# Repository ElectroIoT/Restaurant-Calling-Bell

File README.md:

# Restaurant Calling Bell (SI24R1)

Open-source wireless table-calling system: **10 table remotes** (ATmega328P + SI24R1, coin cell or 2xAAA) and **one counter receiver**
(ATmega328P + SI24R1 + SSD1306 OLED + DFPlayer Mini voice). Application-level acknowledgement, bounded retries, duplicate suppression,
pending calls that survive a power cut.

**Status (2026-10-29): firmware compiles, protocol logic tested in software, no hardware tested yet.** See
[docs/hardware-verification.md](docs/hardware-verification.md) for exactly what is verified. Full plan with advice: open
[docs/plan.html](docs/plan.html) in a browser.

The earlier ATtiny85/STM32 concept is kept in `docs/archive-v0-attiny-stm32/`. Vendor datasheets: `docs/datasheets/`.

## Layout

```
docs/        plan.html, architecture, protocol, radio driver choice, audio, power/safety, battery, assembly, flashing,
             troubleshooting, test plan, EasyEDA guide, hardware verification, datasheets
firmware/    common/ (library: protocol, call table, retry FSM, EEPROM log, radio driver), remote/, receiver/
hardware/    remote/ receiver/ (BOM CSVs, EasyEDA data pack, KiCad REFERENCE boards), diagrams/ (Mermaid + wiring), bom/, tools/
tests/       protocol-tests/ (host C tests + 10-remote simulation), test-results-template.csv
tools/       build_firmware.py, battery_calc.py, make_audio_windows.ps1
```

## Quick start

```bash
python tools/build_firmware.py --quick        # compile one remote + receiver for Uno and PCB targets
python tools/build_firmware.py                # all 22 builds, hex files in build/hex/
python tests/protocol-tests/run_tests.py      # host tests (gcc/clang, or: pip install --target tools/.zig ziglang)
python tools/battery_calc.py                  # battery estimate (assumptions, not measurements)
python hardware/tools/gen_bom.py              # regenerate BOM CSVs from hardware/tools/*_design.py
```

Toolchain used: arduino-cli 1.5.1 (inside Arduino IDE 2), `arduino:avr` 1.8.8 (avr-gcc 7.3). Per-board build properties are in
[docs/flashing-guide.md](docs/flashing-guide.md). Table id: `-DTABLE_ID=n` (1..10, checked at compile time).

## Where to start

1. Read [docs/plan.html](docs/plan.html), then [docs/test-plan.md](docs/test-plan.md).
2. Build the two-Uno prototype ([wiring](hardware/diagrams/wiring.md)) and pass tests 2-9.
3. Lay out the PCBs in EasyEDA Pro from [hardware/*/easyeda](hardware) and [docs/easyeda-guide.md](docs/easyeda-guide.md).
4. Order parts from [hardware/bom/BOM-SUMMARY.md](hardware/bom/BOM-SUMMARY.md) (check the "needs checking" list first).

## Known limits

No range, battery-life or reliability number here is measured. The coin-cell option depends on a sag test you still have to run. DFPlayer pin
order/spacing and the coin-holder polarity are assumptions. No audio files are included. KiCad boards in `hardware/*/kicad` are an
unreviewed auto-routed reference, not a release.

## Licence

MIT, see [LICENSE](LICENSE) (firmware, tools, docs and design data).

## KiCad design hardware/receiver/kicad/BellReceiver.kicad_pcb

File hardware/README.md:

# Hardware

You lay the boards out yourself in **EasyEDA Pro**. Start with [`../docs/easyeda-guide.md`](../docs/easyeda-guide.md).

| Folder | Content |
|---|---|
| `remote/easyeda`, `receiver/easyeda` | netlist, per-pin nets, BOM with LCSC numbers, placement hints (generated from `tools/*_design.py`) |
| `remote/bom`, `receiver/bom`, `bom/` | BOM CSVs (1x, 10x, system) and `BOM-SUMMARY.md` |
| `remote/kicad`, `receiver/kicad` | **reference only**: KiCad 10 schematic and an auto-routed PCB. ERC and DRC were run (0 errors on the last runs, silkscreen warnings only). Not reviewed by a person, not fabricated. |
| `lib/BellParts.pretty` | KiCad footprints for the SI24R1 module, CR2450 holder and tact switch, from vendor drawings (polarity of the holder unknown) |
| `diagrams/` | Mermaid block, sequence and state diagrams, `wiring.md` pin maps |
| `tools/` | generators: schematic/PCB for KiCad (adapted from the NewYearPixelFireworks scripts), `gen_bom.py`, `gen_easyeda_pack.py`; Freerouting jar is not committed |

Single source of truth: `tools/remote_design.py` and `tools/receiver_design.py`.

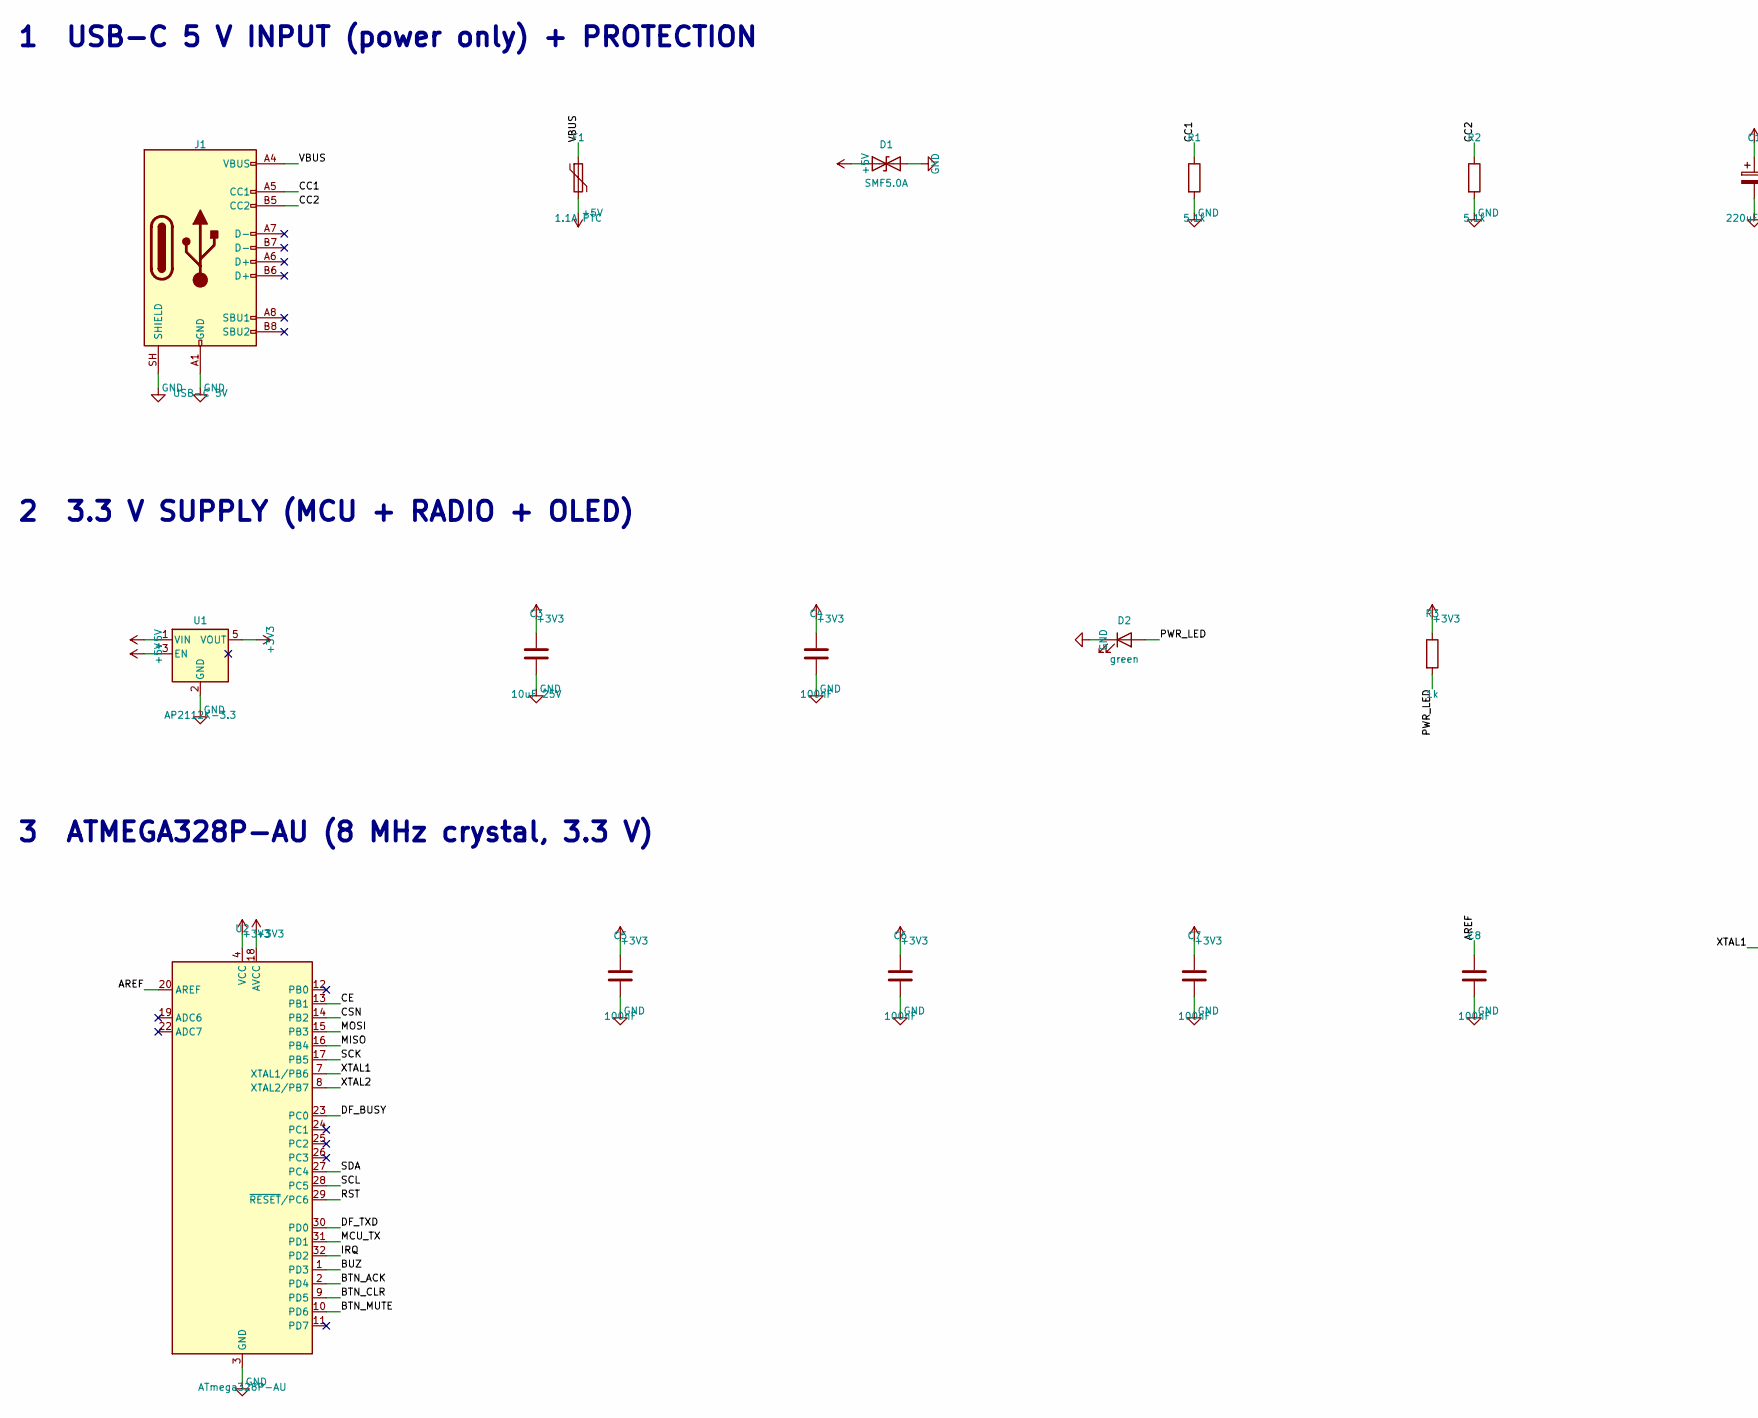
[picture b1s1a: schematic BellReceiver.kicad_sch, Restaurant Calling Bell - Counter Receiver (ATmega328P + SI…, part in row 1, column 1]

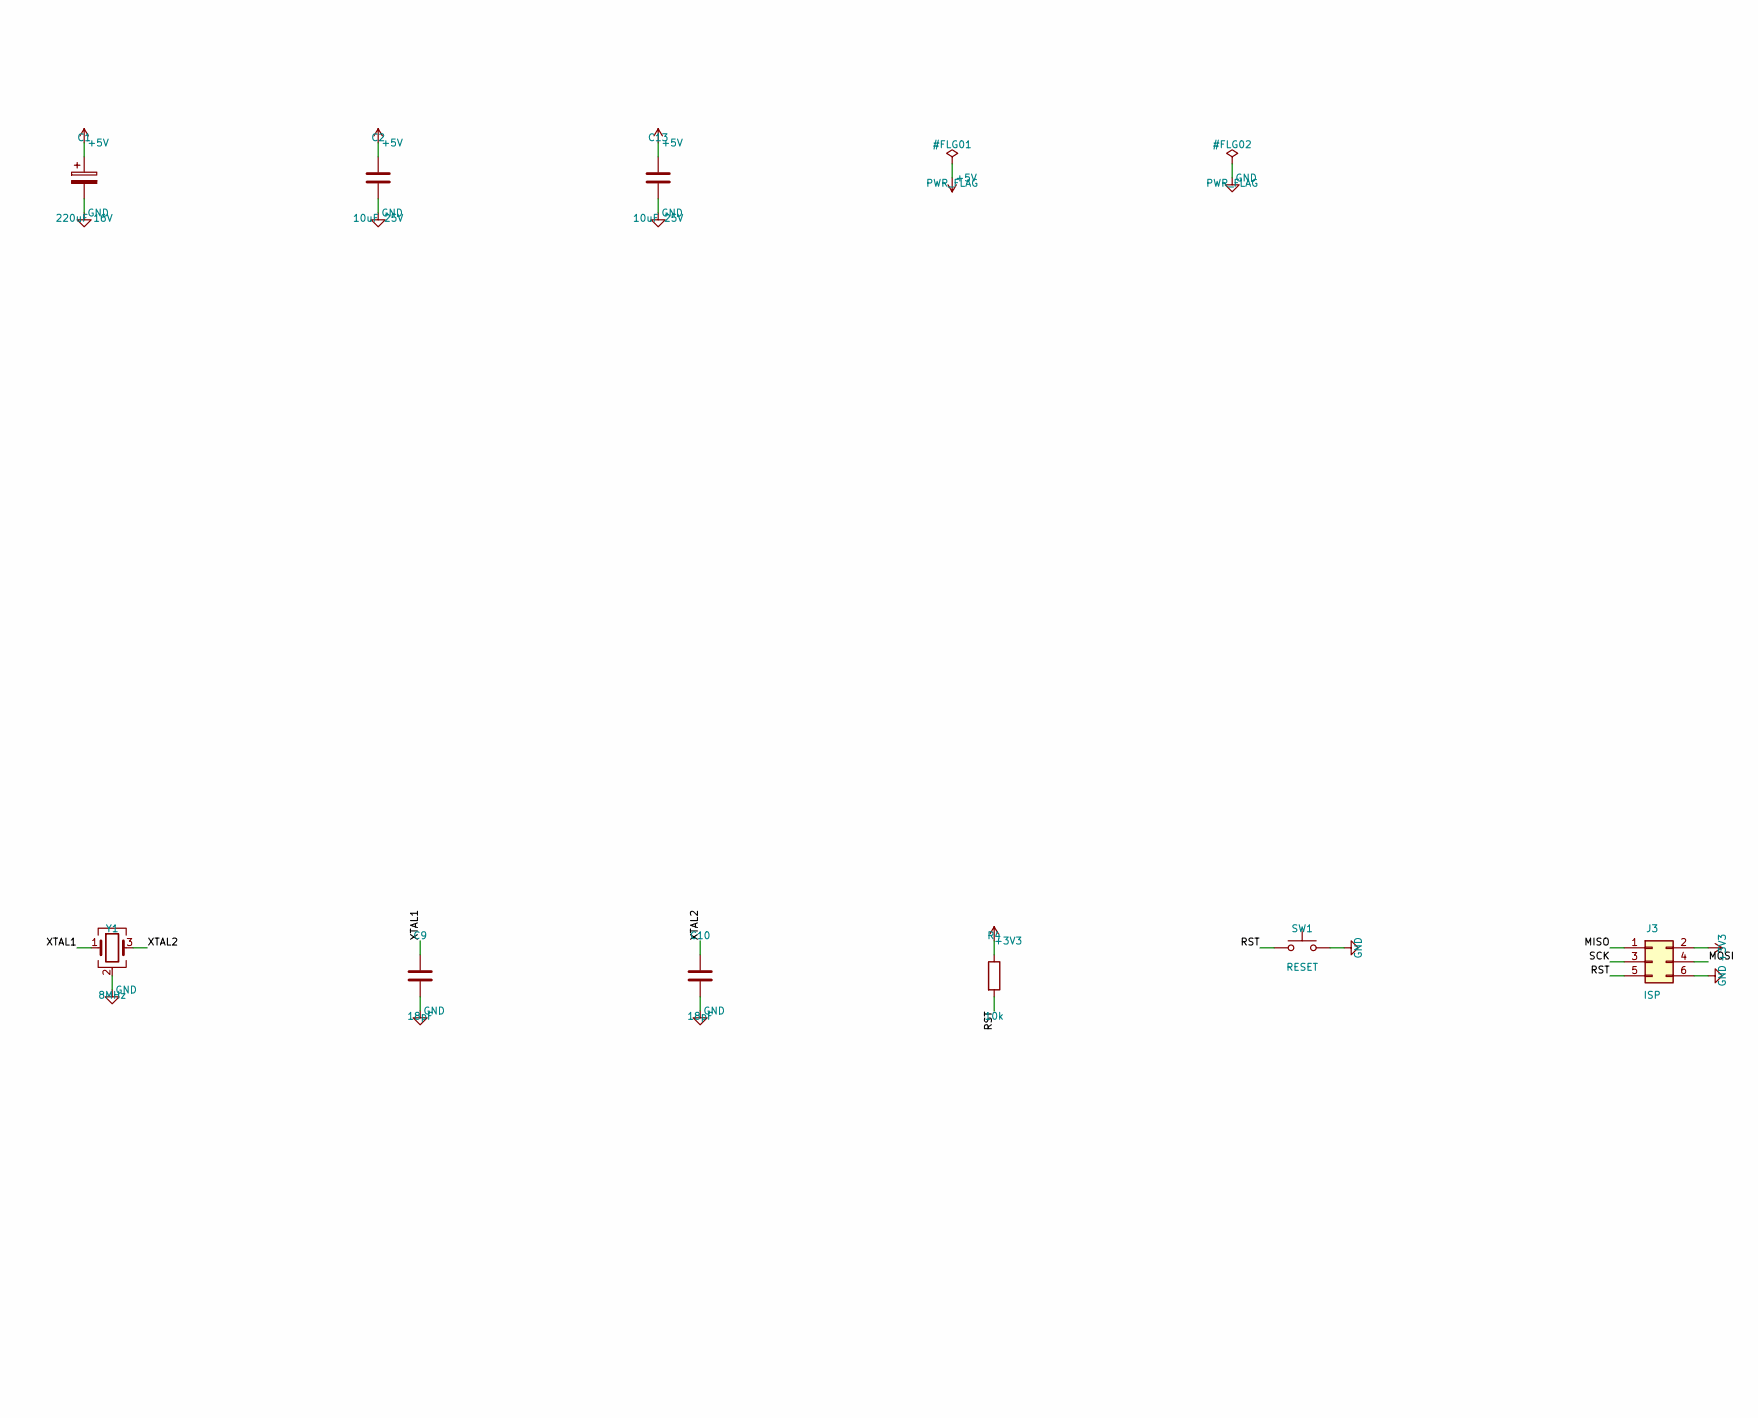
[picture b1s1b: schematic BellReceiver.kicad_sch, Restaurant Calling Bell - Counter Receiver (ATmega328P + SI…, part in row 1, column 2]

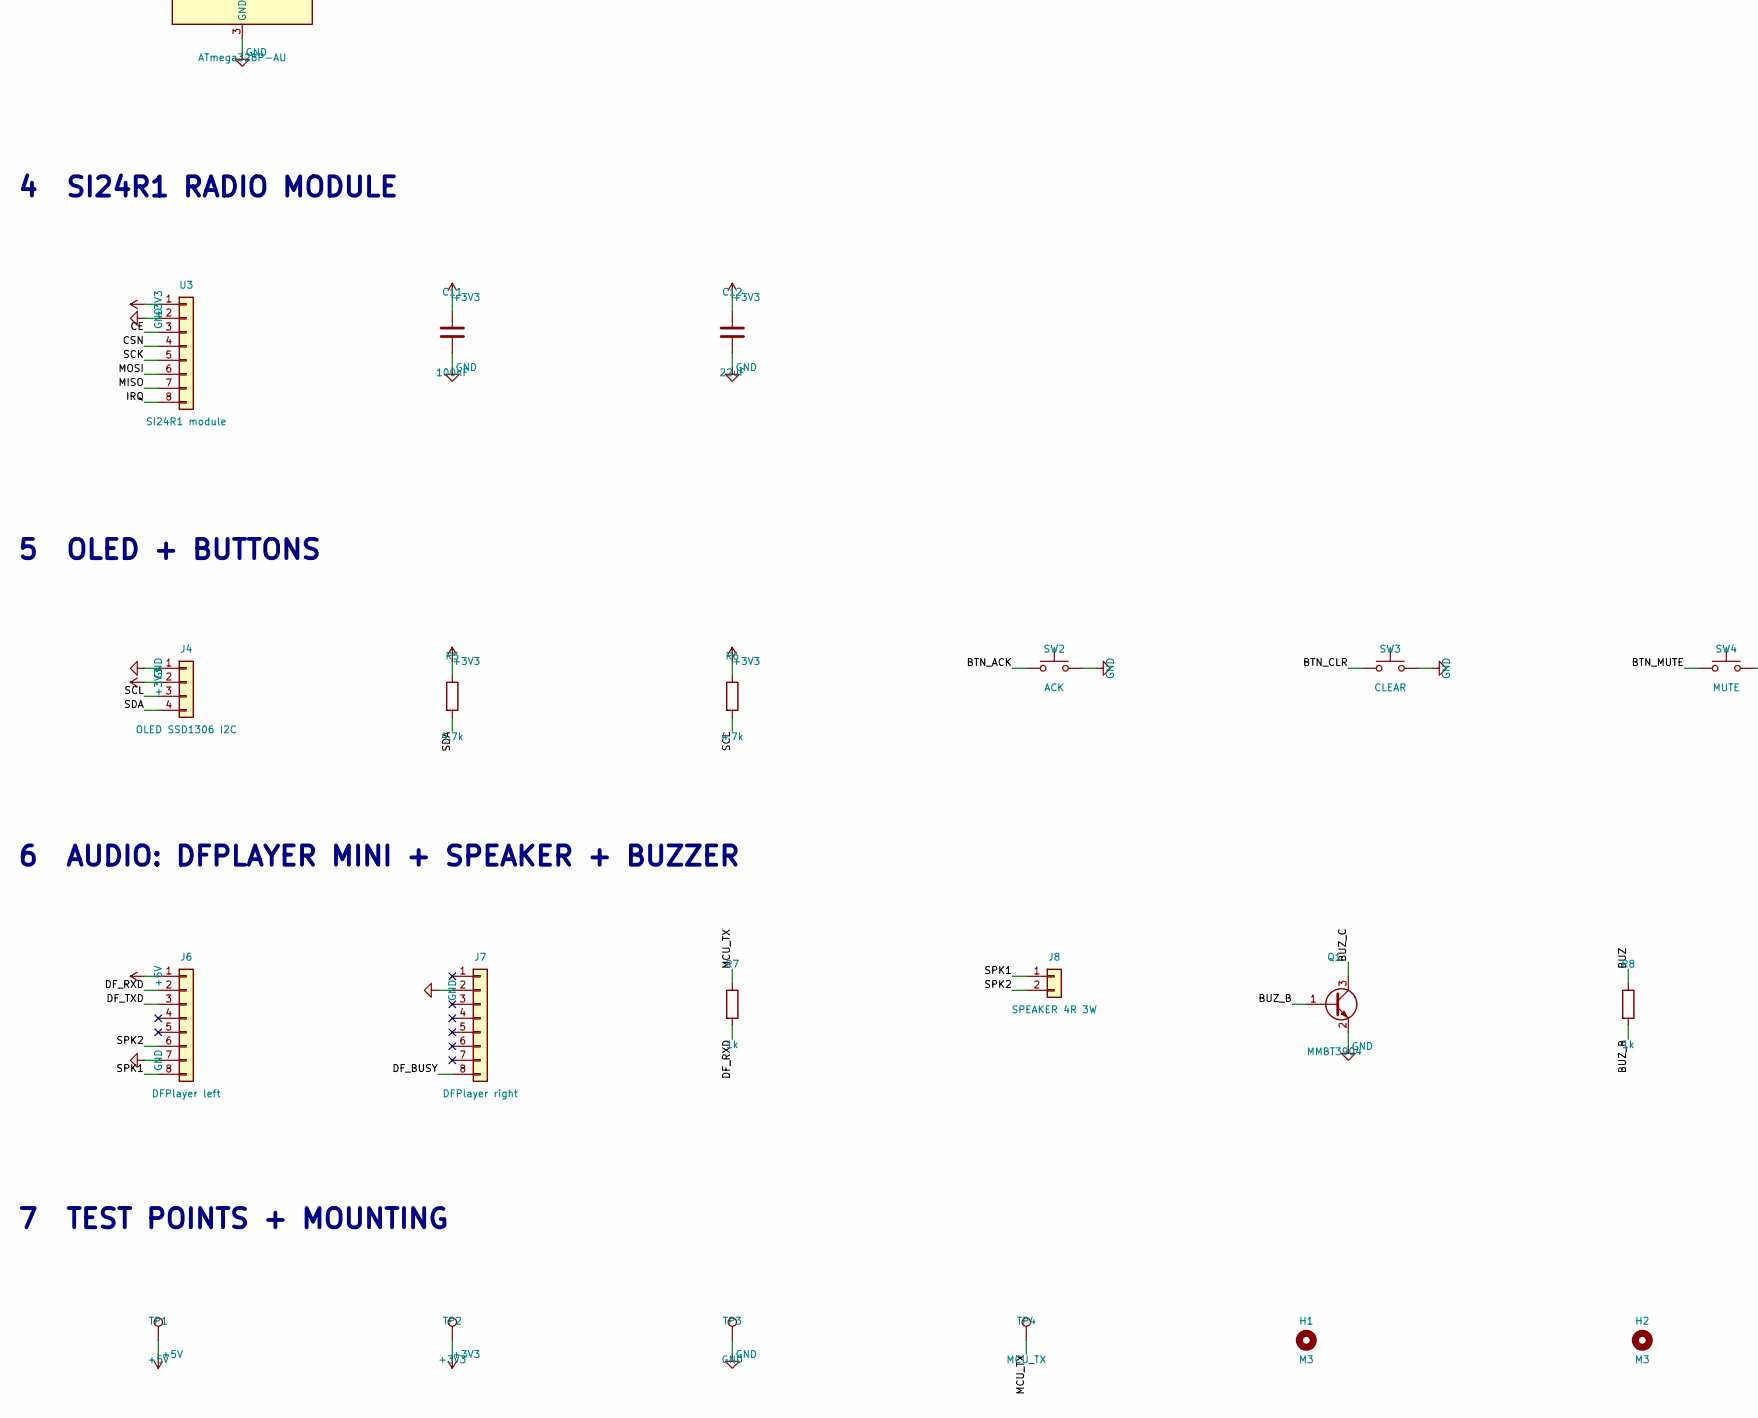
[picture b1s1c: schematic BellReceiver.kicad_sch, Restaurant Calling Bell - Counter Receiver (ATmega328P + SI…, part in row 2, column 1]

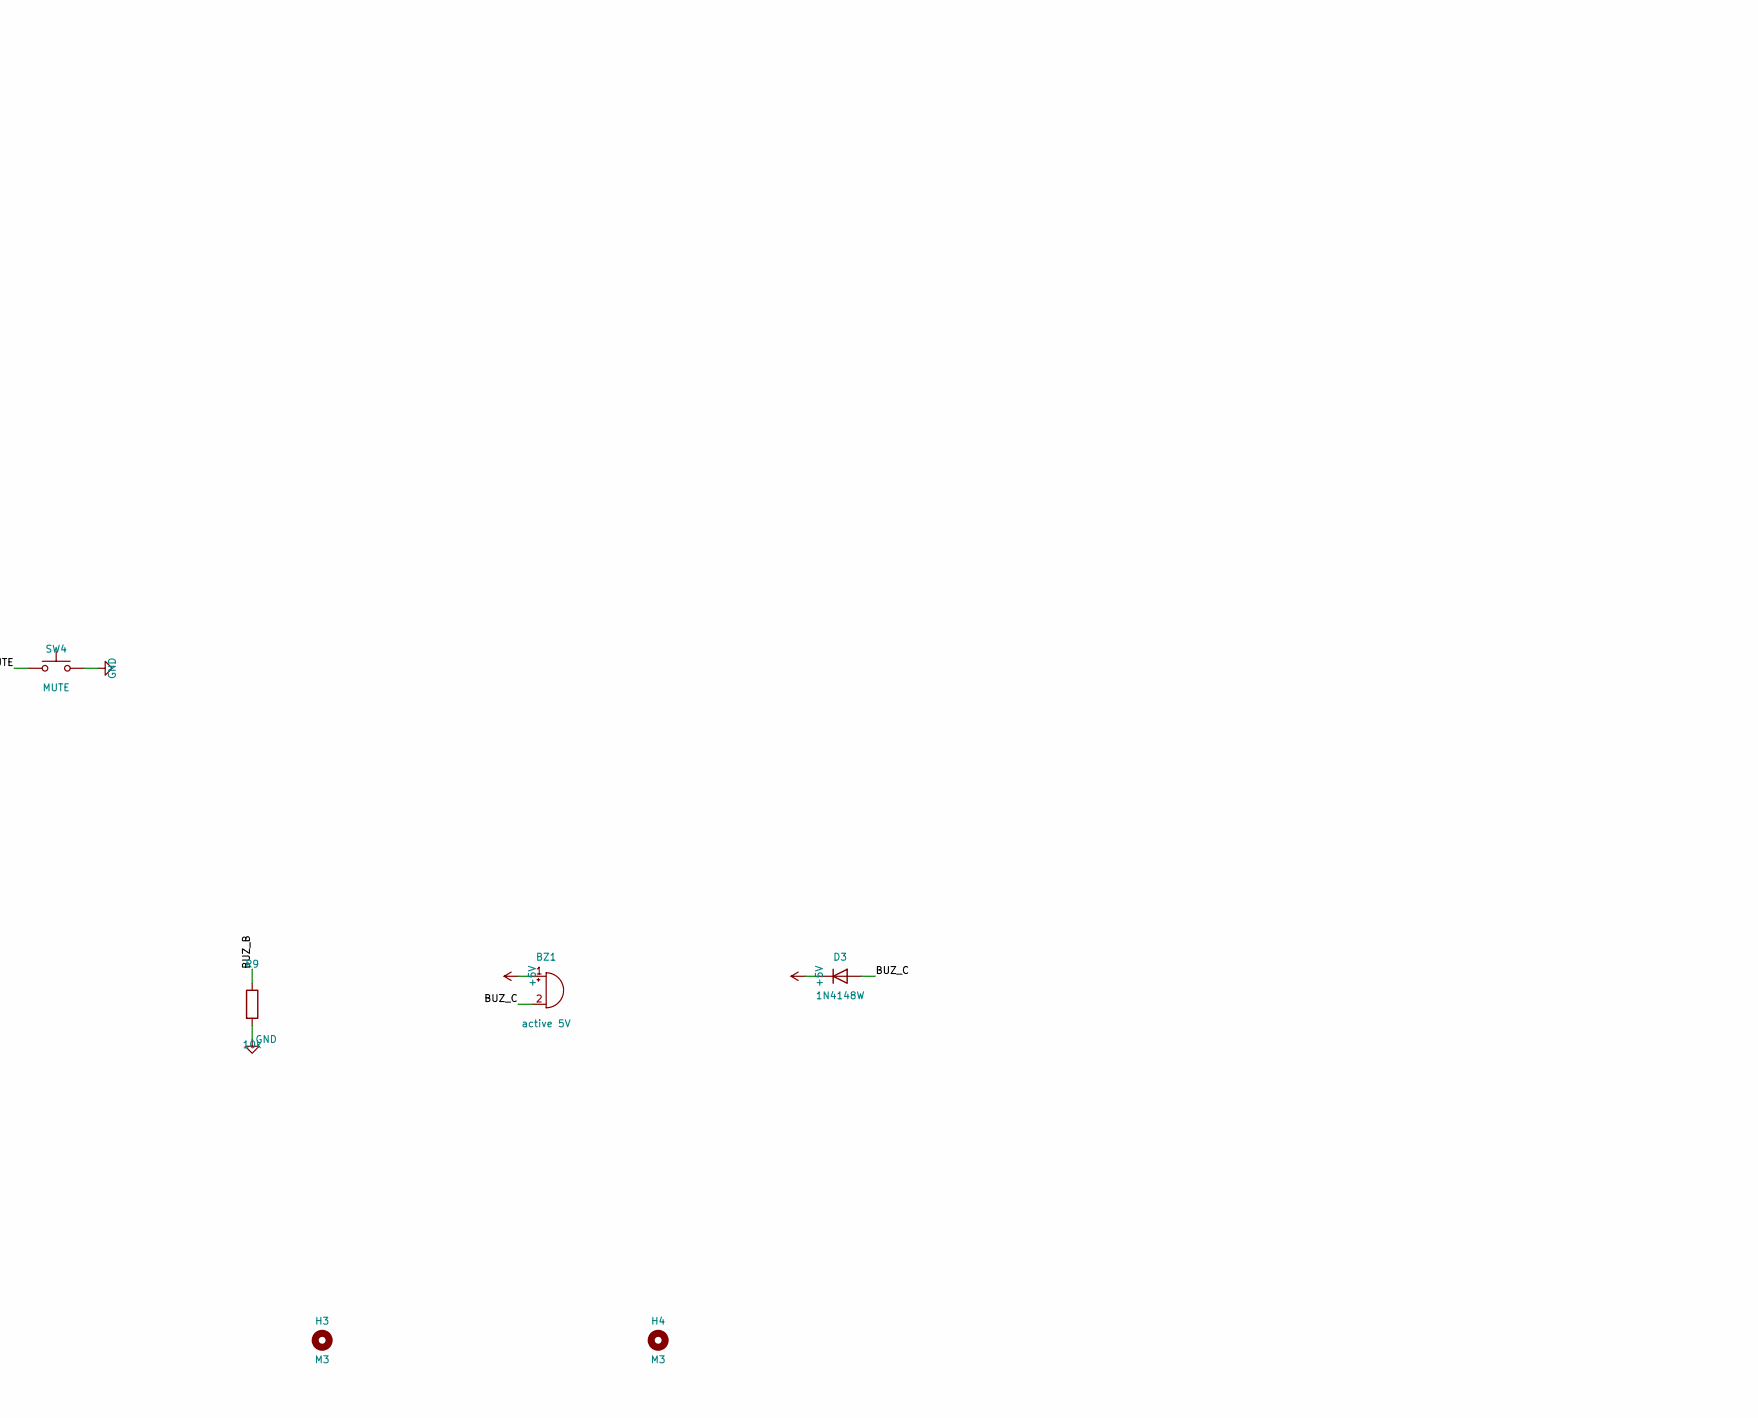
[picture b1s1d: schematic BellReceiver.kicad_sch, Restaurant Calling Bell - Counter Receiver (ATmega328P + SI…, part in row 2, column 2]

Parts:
BZ1: active 5V; Buzzer_12x9.5RM7.6
C1: 220uF 16V; CP_Elec_6.3x7.7
C2, C3, C13: 10uF 25V; C_0805_2012Metric
C4, C5, C6, C7, C8, C11: 100nF; C_0805_2012Metric
C9, C10: 18pF; C_0805_2012Metric
C12: 22uF; C_0805_2012Metric
D1: SMF5.0A; D_SOD-123F
D2: green; LED_0805_2012Metric
D3: 1N4148W; D_SOD-123
F1: 1.1A PTC; Fuse_1206_3216Metric
H1, H2, H3, H4: M3; MountingHole_3.2mm_M3
J1: USB-C 5V; USB_C_Receptacle_HRO_TYPE-C-31-M-12
J3: ISP; PinHeader_2x03_P2.54mm_Vertical
J4: OLED SSD1306 I2C; PinSocket_1x04_P2.54mm_Vertical
J6: DFPlayer left; PinSocket_1x08_P2.54mm_Vertical
J7: DFPlayer right; PinSocket_1x08_P2.54mm_Vertical
J8: SPEAKER 4R 3W; TerminalBlock_MaiXu_MX126-5.0-02P_1x02_P5.00mm
Q1: MMBT3904; SOT-23
R1, R2: 5.1k; R_0805_2012Metric
R3, R7, R8: 1k; R_0805_2012Metric
R4, R9: 10k; R_0805_2012Metric
R5, R6: 4.7k; R_0805_2012Metric
SW1: RESET; SW_TS-1187A
SW2: ACK; SW_TS-1187A
SW3: CLEAR; SW_TS-1187A
SW4: MUTE; SW_TS-1187A
TP1: +5V; TestPoint_Pad_D2.0mm
TP2: +3V3; TestPoint_Pad_D2.0mm
TP3: GND; TestPoint_Pad_D2.0mm
TP4: MCU_TX; TestPoint_Pad_D2.0mm
U1: AP2112K-3.3; SOT-23-5
U2: ATmega328P-AU; TQFP-32_7x7mm_P0.8mm
U3: SI24R1 module; SI24R1_Module_12x18
Y1: 8MHz; Crystal_SMD_3225-4Pin_3.2x2.5mm

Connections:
+3V3: C3.1, C4.1, C5.1, C6.1, C7.1, C11.1, C12.1, J3.2, J4.2, R3.1, R4.1, R5.1, R6.1, TP2.1, U1.5 (VOUT), U2.4 (VCC), U2.6 (VCC), U2.18 (AVCC), U3.1
+5V: BZ1.1 (+), C1.1, C2.1, C13.1, D1.1 (A1), D3.1 (K), F1.2, J6.1, TP1.1, U1.1 (VIN), U1.3 (EN)
AREF: C8.1, U2.20 (AREF)
BTN_ACK: SW2.1, U2.2 (PD4)
BTN_CLR: SW3.1, U2.9 (PD5)
BTN_MUTE: SW4.1, U2.10 (PD6)
BUZ: R8.1, U2.1 (PD3)
BUZ_B: Q1.1 (B), R8.2, R9.1
BUZ_C: BZ1.2 (-), D3.2 (A), Q1.3 (C)
CC1: J1.A5 (CC1), R1.1
CC2: J1.B5 (CC2), R2.1
CE: U2.13 (PB1), U3.3
CSN: U2.14 (PB2), U3.4
DF_BUSY: J7.8, U2.23 (PC0)
DF_RXD: J6.2, R7.2
DF_TXD: J6.3, U2.30 (PD0)
GND: C1.2, C2.2, C3.2, C4.2, C5.2, C6.2, C7.2, C8.2, C9.2, C10.2, C11.2, C12.2, C13.2, D1.2 (A2), D2.1 (K), J1.A1 (GND), J1.A12 (GND), J1.B1 (GND), J1.B12 (GND), J1.SH (SHIELD), J3.6, J4.1, J6.7, J7.2, Q1.2 (E), R1.2, R2.2, R9.2, SW1.2, SW2.2, SW3.2, SW4.2, TP3.1, U1.2 (GND), U2.3 (GND), U2.5 (GND), U2.21 (GND), U3.2, Y1.2 (G), Y1.4 (G)
IRQ: U2.32 (PD2), U3.8
MCU_TX: R7.1, TP4.1, U2.31 (PD1)
MISO: J3.1, U2.16 (PB4), U3.7
MOSI: J3.4, U2.15 (PB3), U3.6
PWR_LED: D2.2 (A), R3.2
RST: J3.5, R4.2, SW1.1, U2.29 (~RESET/PC6)
SCK: J3.3, U2.17 (PB5), U3.5
SCL: J4.3, R6.2, U2.28 (PC5)
SDA: J4.4, R5.2, U2.27 (PC4)
SPK1: J6.8, J8.1
SPK2: J6.6, J8.2
VBUS: F1.1, J1.A4 (VBUS), J1.A9 (VBUS), J1.B4 (VBUS), J1.B9 (VBUS)
XTAL1: C9.1, U2.7 (XTAL1/PB6), Y1.1
XTAL2: C10.1, U2.8 (XTAL2/PB7), Y1.3

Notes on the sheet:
1 USB-C 5 V INPUT (power only) + PROTECTION
2 3.3 V SUPPLY (MCU + RADIO + OLED)
3 ATMEGA328P-AU (8 MHz crystal, 3.3 V)
4 SI24R1 RADIO MODULE
5 OLED + BUTTONS
6 AUDIO: DFPLAYER MINI + SPEAKER + BUZZER
7 TEST POINTS + MOUNTING

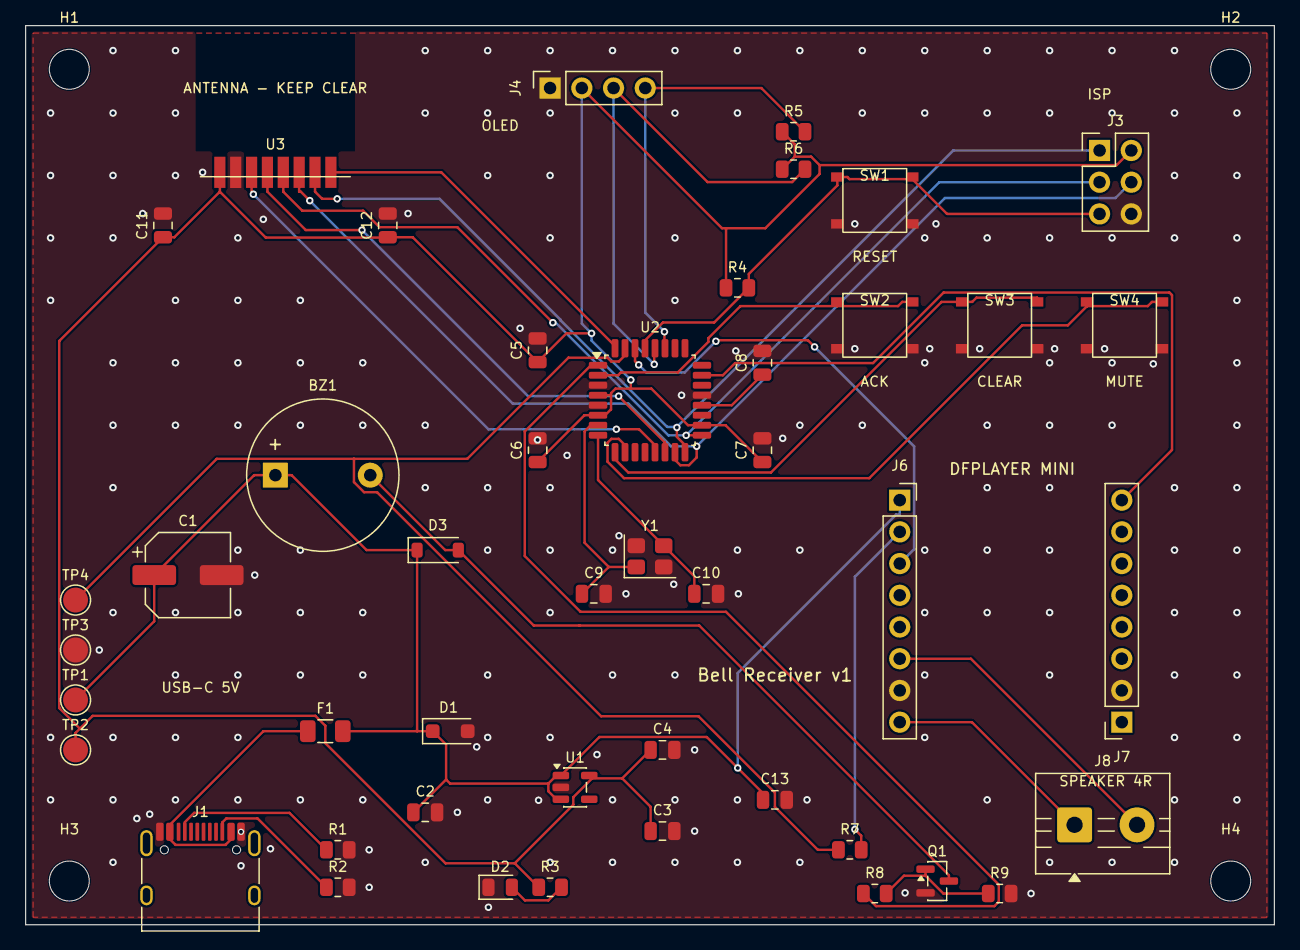
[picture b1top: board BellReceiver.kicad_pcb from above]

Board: 2 copper layers, 100.0 x 72.0 mm, 50 parts (0 on the bottom side), 31 nets.

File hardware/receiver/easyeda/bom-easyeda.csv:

Designator,Footprint,Quantity,Value,Manufacturer Part,Manufacturer,Supplier Part,Supplier
BZ1,Buzzer_12x9.5RM7.6,1,active 5V,TMB12A05,Huaneng,C96093,LCSC
C1,CP_Elec_6.3x7.7,1,220uF 16V,RVT220UF16V67RV0015,KNSCHA,C2887273,LCSC
C12,C_0805_2012Metric,1,22uF,CL21A226MQQNNNE,Samsung,C5674,LCSC
"C2,C3,C13",C_0805_2012Metric,3,10uF 25V,CL21A106KAYNNNE,Samsung,C15850,LCSC
"C4,C5,C6,C7,C8,C11",C_0805_2012Metric,6,100nF,CL21B104KBCNNNC,Samsung,C1711,LCSC
"C9,C10",C_0805_2012Metric,2,18pF,CC0805JRNPO9BN180,Yageo,C113825,LCSC
D1,D_SOD-123F,1,SMF5.0A,SMF5.0A,MDD,C193402,LCSC
D2,LED_0805_2012Metric,1,green,KT-0805G,Hubei KENTO,C2297,LCSC
D3,D_SOD-123,1,1N4148W,1N4148W,PANJIT,C304038,LCSC
F1,Fuse_1206_3216Metric,1,1.1A PTC,1206L110THYR,Littelfuse,C126818,LCSC
J1,USB_C_Receptacle_HRO_TYPE-C-31-M-12,1,USB-C 5V,TYPE-C-31-M-12,Korean Hroparts Elec,C165948,LCSC
J3,PinHeader_2x03_P2.54mm_Vertical,1,ISP,PZ254V-12-06P-T,XFCN,C56153599,LCSC
J4,PinSocket_1x04_P2.54mm_Vertical,1,OLED SSD1306 I2C,PM254-1-04-Z-8.5,HCTL,C2897367,LCSC
J6,PinSocket_1x08_P2.54mm_Vertical,1,DFPlayer left,PM254-1-08-Z-8.5,HCTL,C2897371,LCSC
J7,PinSocket_1x08_P2.54mm_Vertical,1,DFPlayer right,PM254-1-08-Z-8.5,HCTL,C2897371,LCSC
J8,TerminalBlock_MaiXu_MX126-5.0-02P_1x02_P5.00mm,1,SPEAKER 4R 3W,KF301-5.0-2P,Cixi Kefa,C474881,LCSC
Q1,SOT-23,1,MMBT3904,MMBT3904LT1G,onsemi,C81464,LCSC
"R1,R2",R_0805_2012Metric,2,5.1k,0805W8F5101T5E,UNI-ROYAL,C27834,LCSC
"R3,R7,R8",R_0805_2012Metric,3,1k,0805W8F1001T5E,UNI-ROYAL,C17513,LCSC
"R4,R9",R_0805_2012Metric,2,10k,0805W8F1002T5E,UNI-ROYAL,C17414,LCSC
"R5,R6",R_0805_2012Metric,2,4.7k,0805W8F4701T5E,UNI-ROYAL,C17673,LCSC
SW1,SW_TS-1187A,1,RESET,TS-1187A-B-A-B,XKB Connection,C318884,LCSC
SW2,SW_TS-1187A,1,ACK,TS-1187A-B-A-B,XKB Connection,C318884,LCSC
SW3,SW_TS-1187A,1,CLEAR,TS-1187A-B-A-B,XKB Connection,C318884,LCSC
SW4,SW_TS-1187A,1,MUTE,TS-1187A-B-A-B,XKB Connection,C318884,LCSC
U1,SOT-23-5,1,AP2112K-3.3,AP2112K-3.3TRG1,Diodes Inc.,C51118,LCSC
U2,TQFP-32_7x7mm_P0.8mm,1,ATmega328P-AU,ATMEGA328P-AU,Microchip,C14877,LCSC
Y1,Crystal_SMD_3225-4Pin_3.2x2.5mm,1,8MHz,XC32M4-8.000-F18LJDT,HCI,C2905353,LCSC

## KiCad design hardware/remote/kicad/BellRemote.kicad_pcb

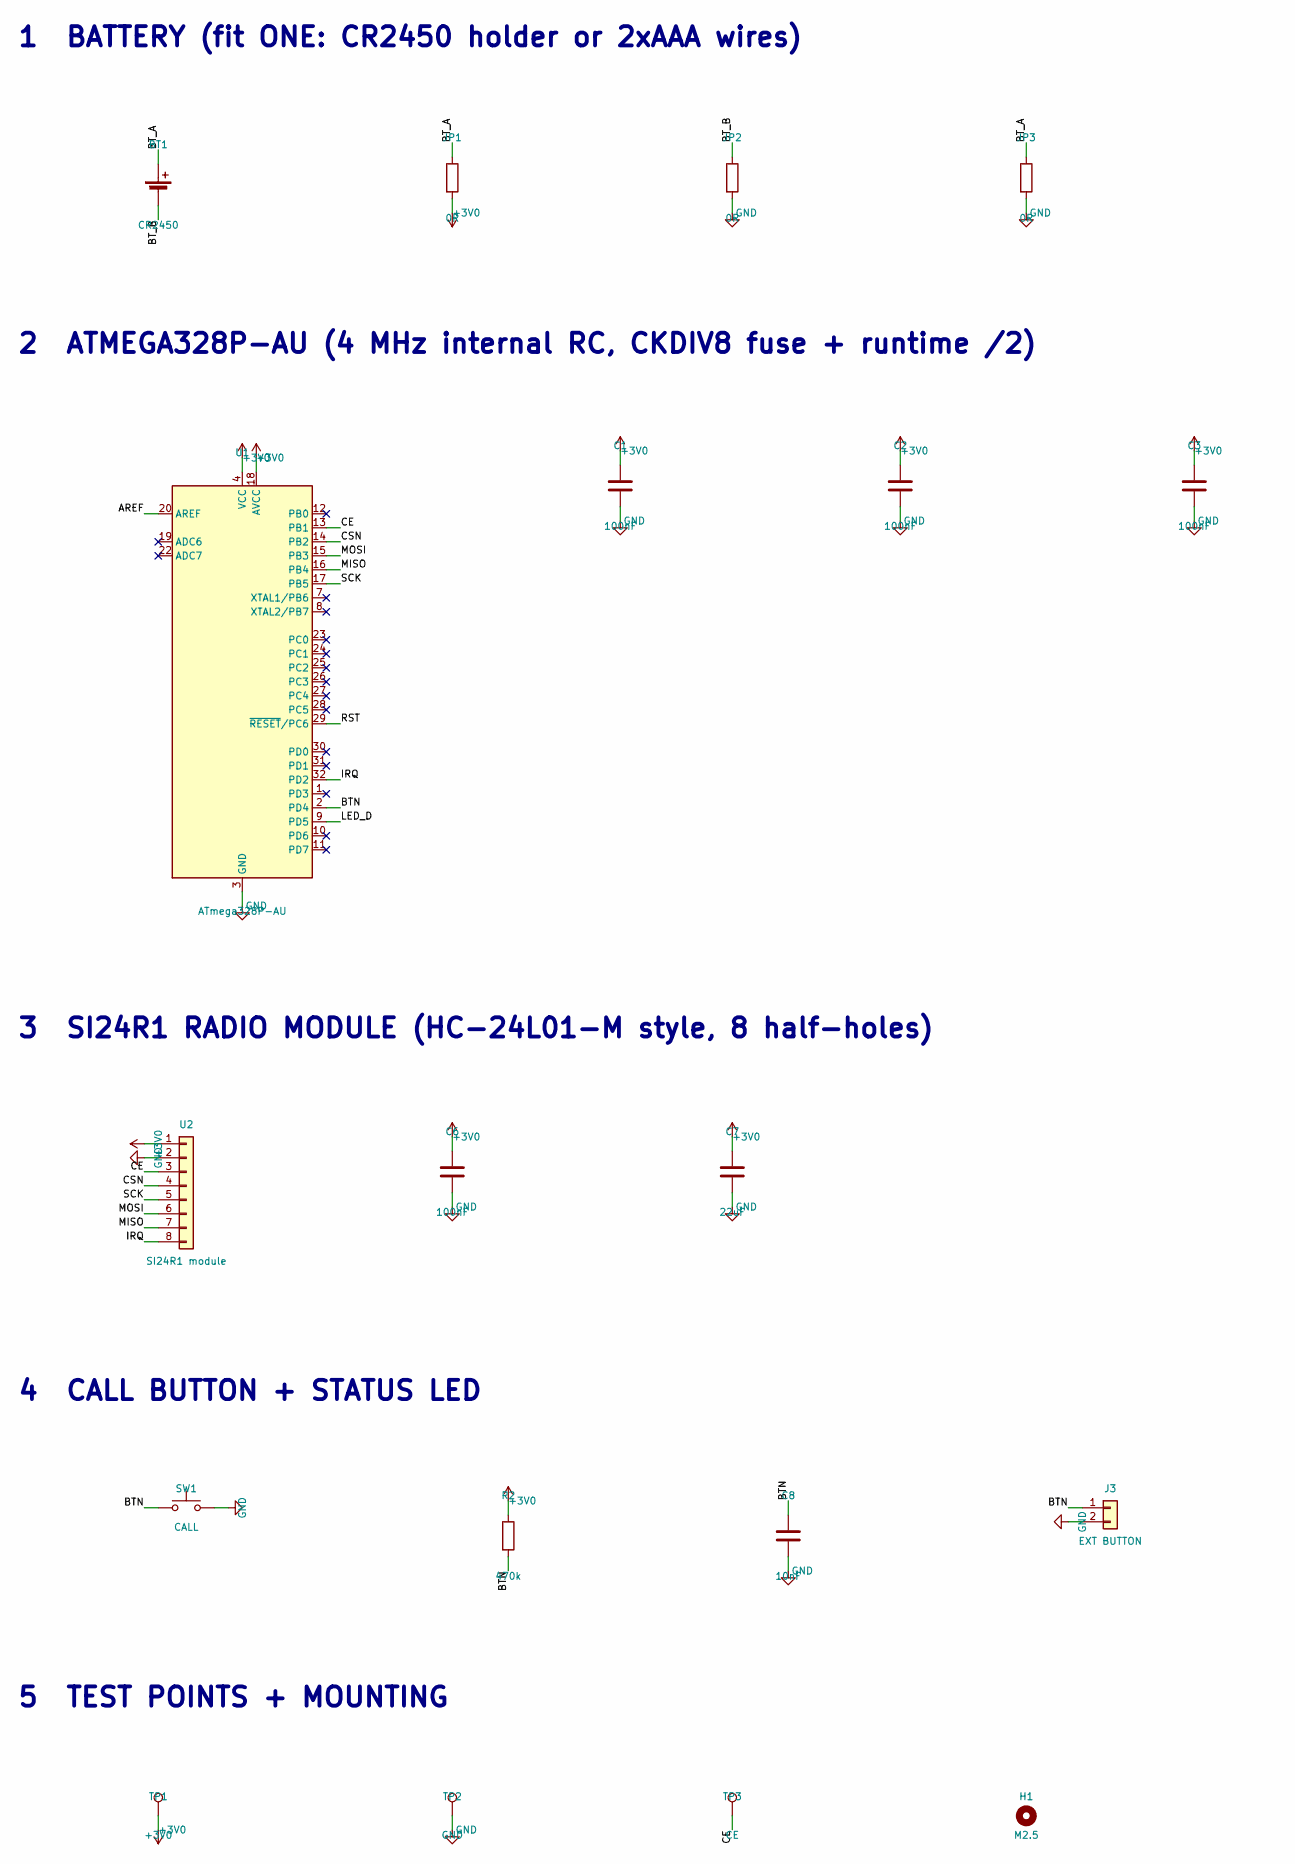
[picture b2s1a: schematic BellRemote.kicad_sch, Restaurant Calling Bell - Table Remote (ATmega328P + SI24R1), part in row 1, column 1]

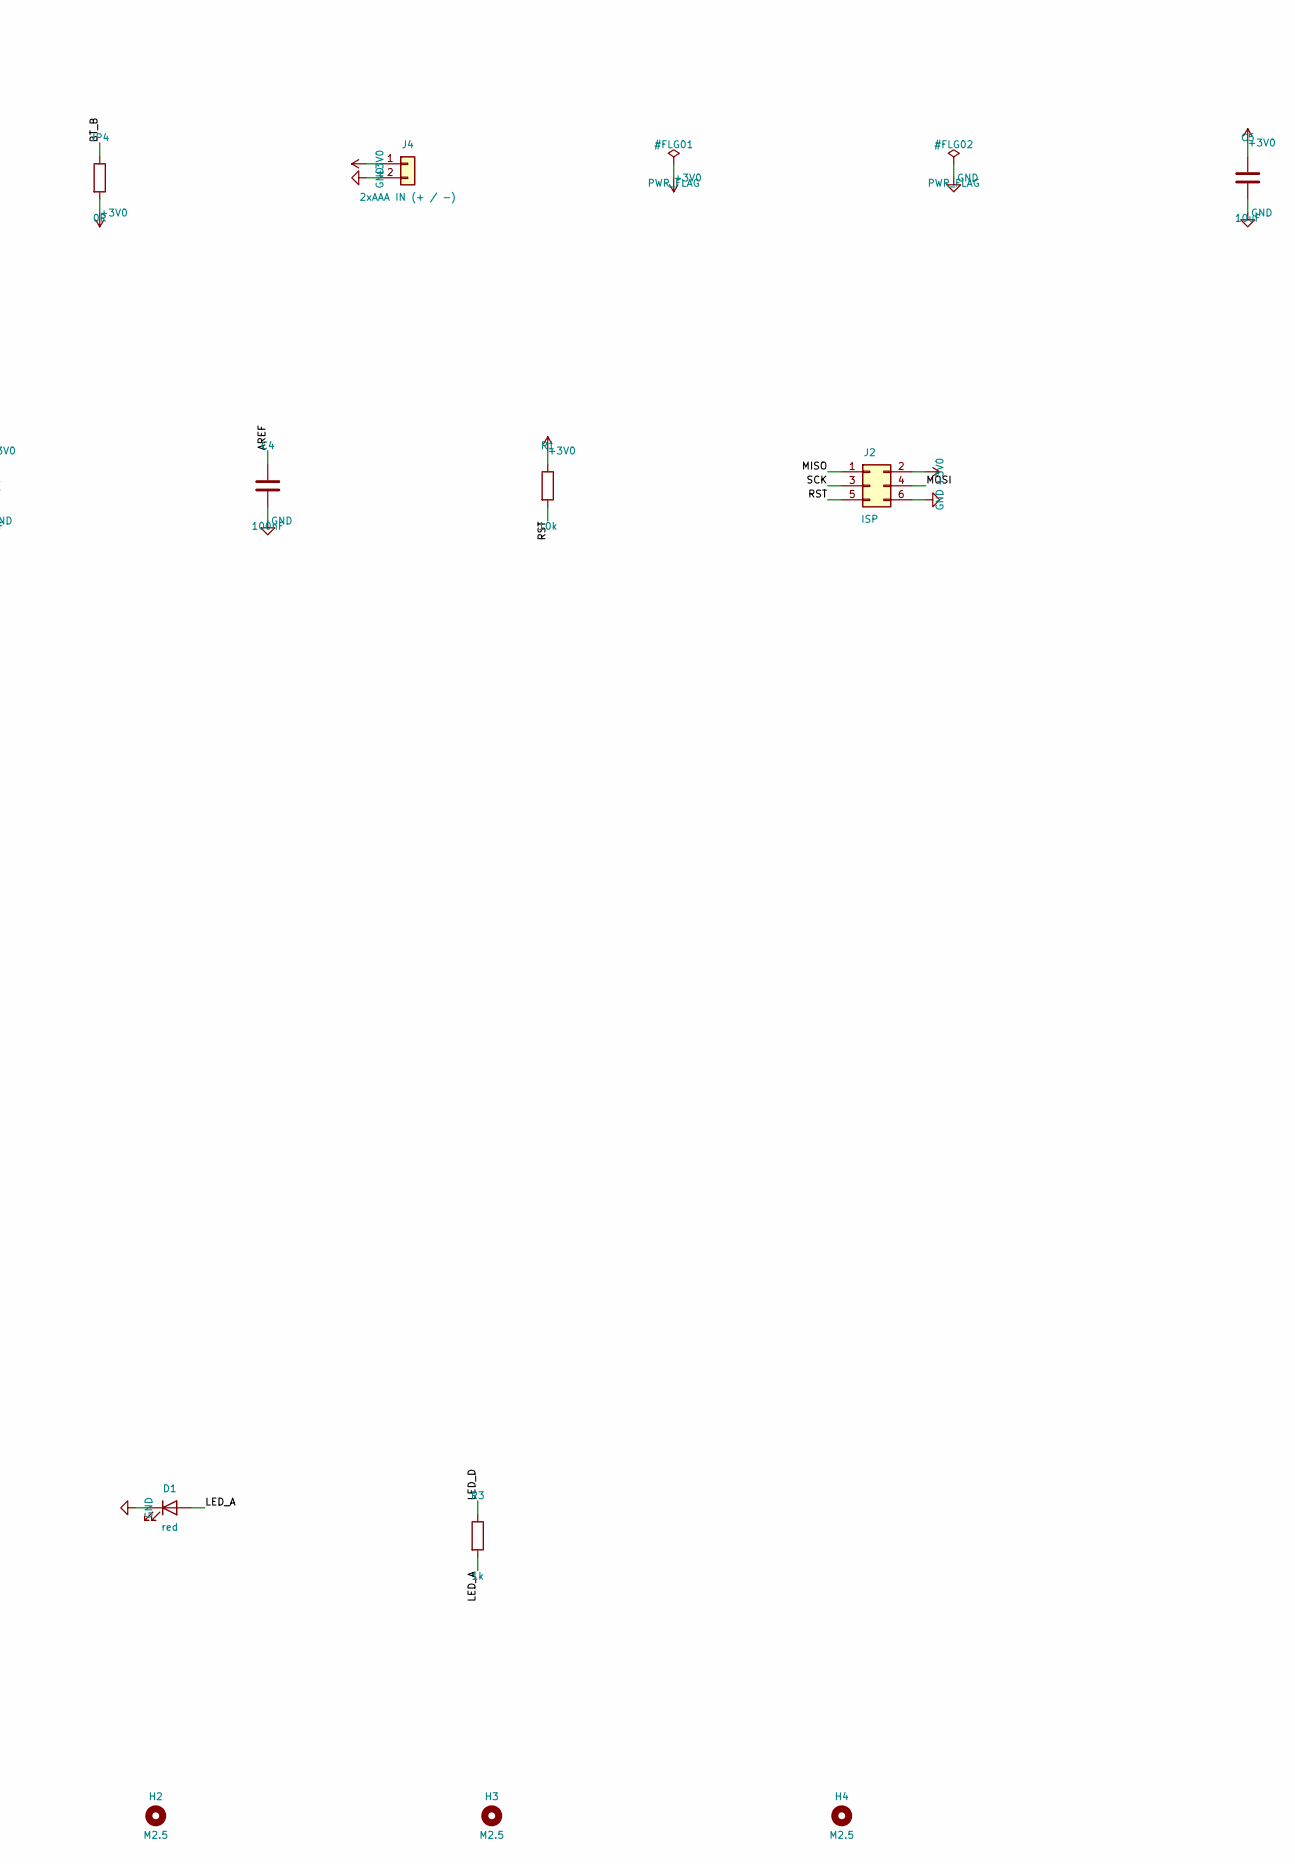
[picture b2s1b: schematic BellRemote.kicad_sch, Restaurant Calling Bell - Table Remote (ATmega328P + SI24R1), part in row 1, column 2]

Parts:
BT1: CR2450; CR2450_Holder_MY-2450-01
C1, C2, C3, C4, C6: 100nF; C_0805_2012Metric
C5: 10uF; C_0805_2012Metric
C7: 22uF; C_0805_2012Metric
C8: 10nF; C_0805_2012Metric
D1: red; LED_0805_2012Metric
H1, H2, H3, H4: M2.5; MountingHole_2.7mm_M2.5
J2: ISP; PinHeader_2x03_P2.54mm_Vertical
J3: EXT BUTTON; PinHeader_1x02_P2.54mm_Vertical
J4: 2xAAA IN (+ / -); PinHeader_1x02_P2.54mm_Vertical
JP1, JP2, JP3, JP4: 0R; R_0805_2012Metric
R1: 10k; R_0805_2012Metric
R2: 470k; R_0805_2012Metric
R3: 1k; R_0805_2012Metric
SW1: CALL; SW_TS-1187A
TP1: +3V0; TestPoint_Pad_D2.0mm
TP2: GND; TestPoint_Pad_D2.0mm
TP3: CE; TestPoint_Pad_D2.0mm
U1: ATmega328P-AU; TQFP-32_7x7mm_P0.8mm
U2: SI24R1 module; SI24R1_Module_12x18

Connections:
+3V0: C1.1, C2.1, C3.1, C5.1, C6.1, C7.1, J2.2, J4.1, JP1.2, JP4.2, R1.1, R2.1, TP1.1, U1.4 (VCC), U1.6 (VCC), U1.18 (AVCC), U2.1
AREF: C4.1, U1.20 (AREF)
BTN: C8.1, J3.1, R2.2, SW1.1, U1.2 (PD4)
BT_A: BT1.1 (+), JP1.1, JP3.1
BT_B: BT1.2 (-), JP2.1, JP4.1
CE: TP3.1, U1.13 (PB1), U2.3
CSN: U1.14 (PB2), U2.4
GND: C1.2, C2.2, C3.2, C4.2, C5.2, C6.2, C7.2, C8.2, D1.1 (K), J2.6, J3.2, J4.2, JP2.2, JP3.2, SW1.2, TP2.1, U1.3 (GND), U1.5 (GND), U1.21 (GND), U2.2
IRQ: U1.32 (PD2), U2.8
LED_A: D1.2 (A), R3.2
LED_D: R3.1, U1.9 (PD5)
MISO: J2.1, U1.16 (PB4), U2.7
MOSI: J2.4, U1.15 (PB3), U2.6
RST: J2.5, R1.2, U1.29 (~RESET/PC6)
SCK: J2.3, U1.17 (PB5), U2.5

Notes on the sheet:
1 BATTERY (fit ONE: CR2450 holder or 2xAAA wires)
2 ATMEGA328P-AU (4 MHz internal RC, CKDIV8 fuse + runtime /2)
3 SI24R1 RADIO MODULE (HC-24L01-M style, 8 half-holes)
4 CALL BUTTON + STATUS LED
5 TEST POINTS + MOUNTING
